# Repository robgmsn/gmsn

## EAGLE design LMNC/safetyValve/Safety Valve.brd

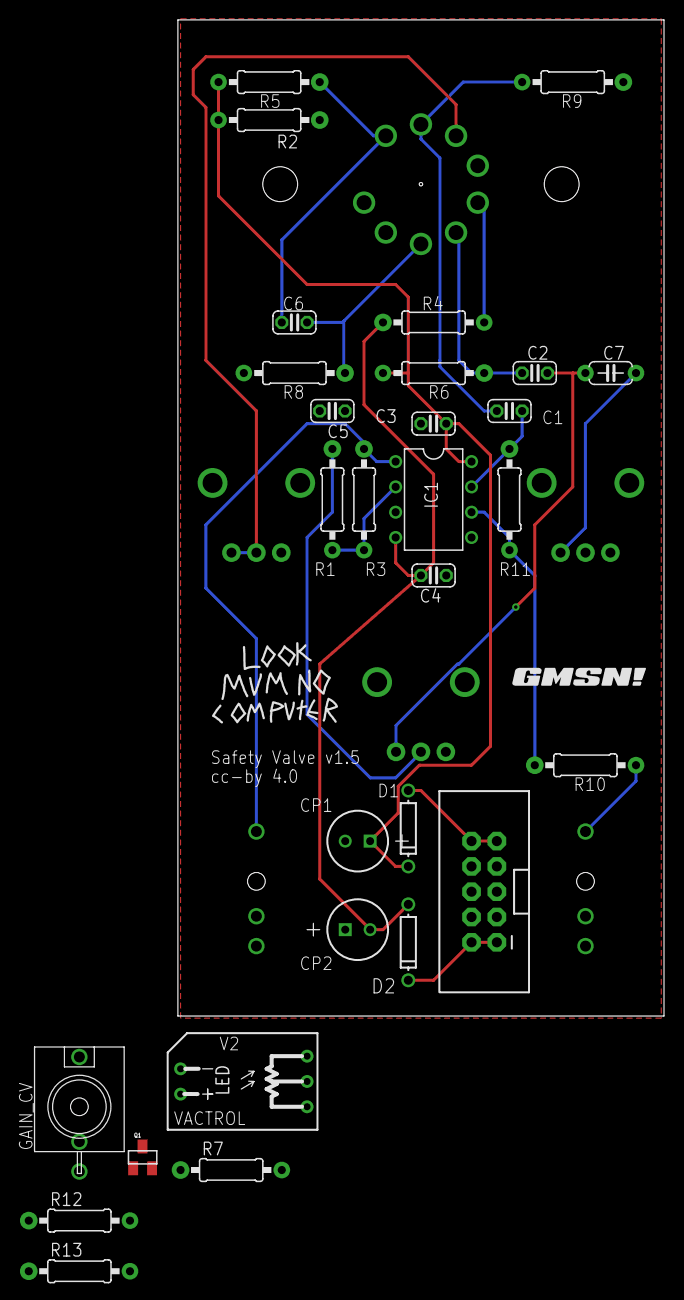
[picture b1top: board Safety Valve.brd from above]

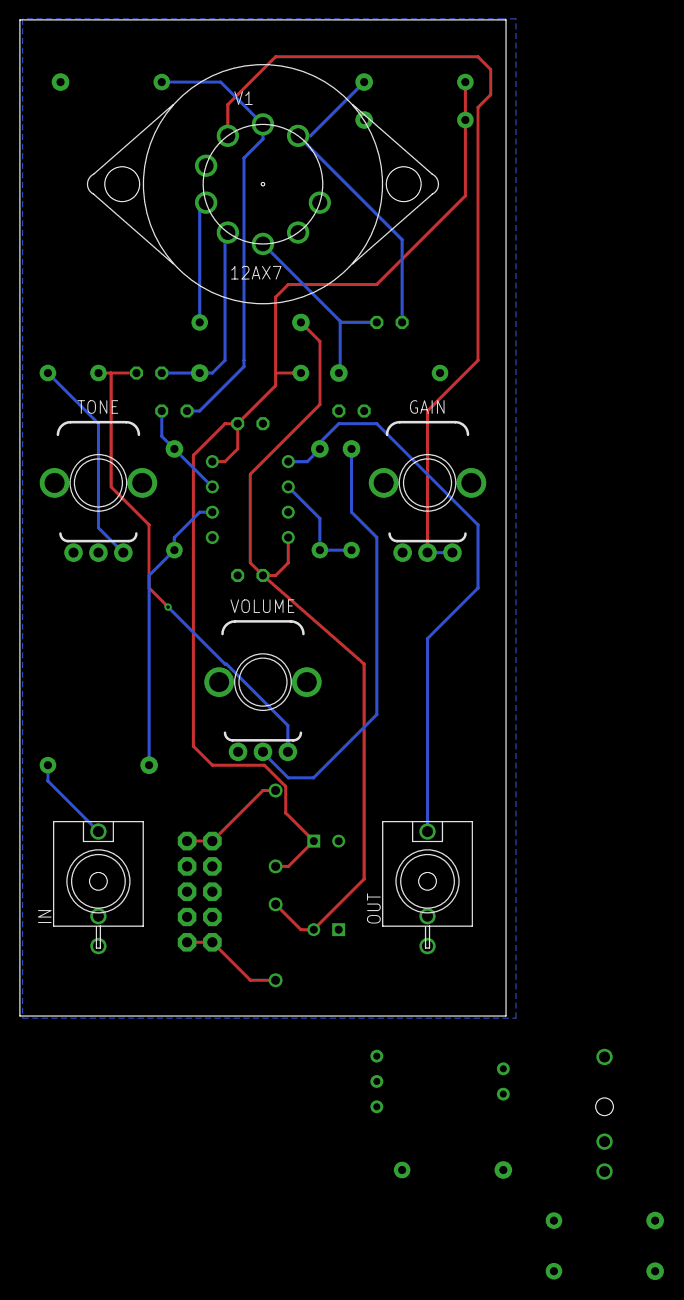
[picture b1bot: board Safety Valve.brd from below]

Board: 2 copper layers, 48.8 x 100.0 mm, 37 parts (6 on the bottom side), 23 nets.

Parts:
C1, C2, C6: 47nF; C025-024X044
C3, C4: 100nF; C025-024X044
C5: 100pF; C025-024X044
C7: 1uF; C050-024X044
CP1, CP2: 10u; SANYO-OSCON_D
D1, D2: 1N4001; DO-41
GAIN: 10k; POTENTIOMETER_9MM
GAIN_CV: SOCKET_MONO_3.5MMPJ301M-12; PJ301M-12
IC1: TL072; DIL08
IN: SOCKET_MONO_3.5MMPJ301M-12; PJ301M-12
JP1: HEADER2X5SHD; 2X5-SHROUDED
OUT: SOCKET_MONO_3.5MMPJ301M-12; PJ301M-12
Q1: SOT23
R1: 470R; 0207/10
R2: 47k; 0207/10
R3: 1M; 0207/10
R4: 27; 0207/10
R5, R6: 12k; 0207/10
R7: 1k; 0207/10
R8, R9: 470k; 0207/10
R10, R11, R12, R13: 100k; 0207/10
TONE: 5k; POTENTIOMETER_9MM
U$1: LMNC_LOGO
U$2: GMSN!_LOGO
V1: 12AX7
V2: VTL5C-2
VOLUME: 100k; POTENTIOMETER_9MM

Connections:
+12V: C3.1, CP1.+, D1.C, IC1.8, R2.2, R5.2, R6.2
-12V: C4.2, CP2.-, D2.A, IC1.4, R4.1
GND: C3.2, C4.1, CP1.-, CP2.+, GAIN.P$1, GAIN_CV.GND, IC1.3, IC1.5, IN.GND, JP1.3, JP1.4, JP1.5, JP1.6, JP1.7, JP1.8, OUT.GND, Q1.2, R8.2, R9.1, R12.1, TONE.P$1, TONE.P$2, V1.P$4, V1.P$8, V2.1, V2.4, VOLUME.P$1
unnamed: GAIN.P$2, GAIN.P$3, V1.P$3, V2.3
unnamed: C5.1, IC1.2, R1.2, R3.2
unnamed: C2.2, C7.1, VOLUME.P$3
unnamed: C5.2, IC1.1, OUT.TIP, R3.1
unnamed: C2.1, R6.1, V1.P$6
unnamed: C6.1, R5.1, V1.P$1
unnamed: C1.2, R2.1, R9.2, V1.P$2
unnamed: C1.1, IC1.7, R11.1
unnamed: R4.2, V1.P$5
unnamed: C6.2, R8.1, V1.P$7
unnamed: D1.A, JP1.9, JP1.10
unnamed: IN.TIP, R10.2
unnamed: D2.C, JP1.1, JP1.2
unnamed: C7.2, TONE.P$3
unnamed: IC1.6, R10.1, R11.2
unnamed: R1.1, VOLUME.P$2
unnamed: GAIN_CV.TIP, R13.1
unnamed: Q1.1, R12.2, R13.2
unnamed: R7.2, V2.2
unnamed: Q1.3, R7.1

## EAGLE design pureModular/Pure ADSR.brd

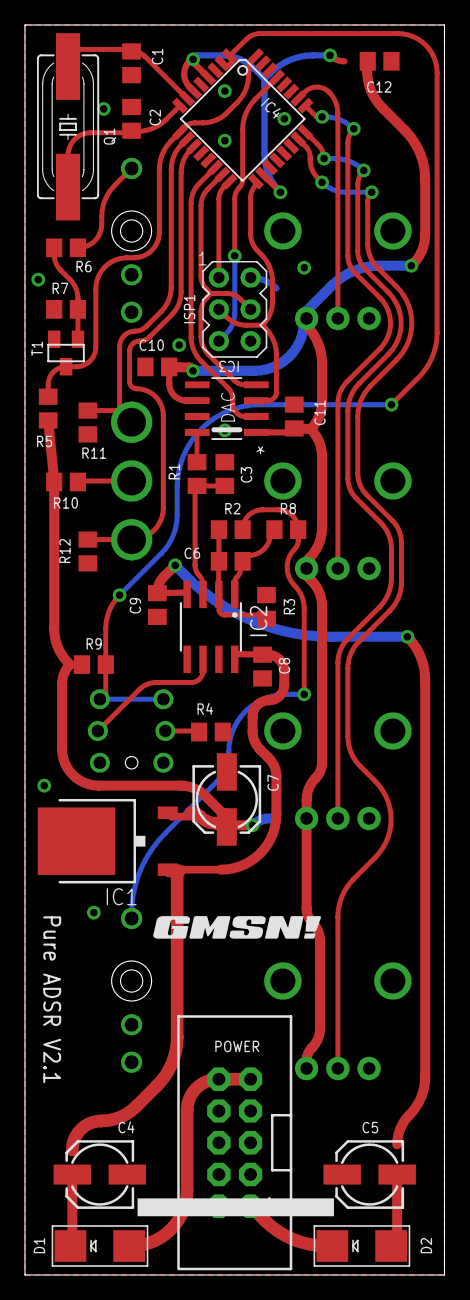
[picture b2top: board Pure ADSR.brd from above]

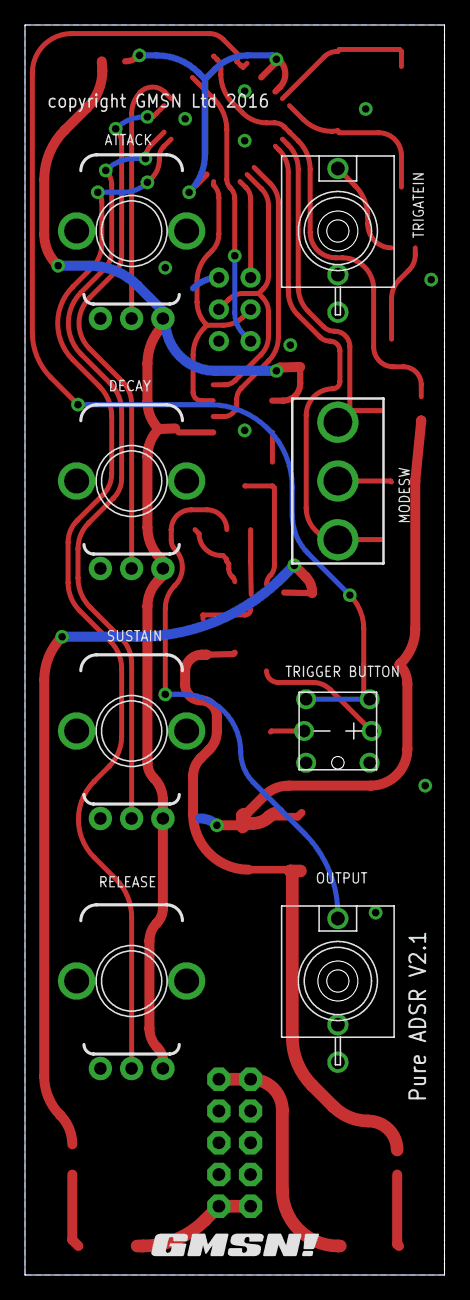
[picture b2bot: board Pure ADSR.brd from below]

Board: 2 copper layers, 33.6 x 100.0 mm, 44 parts (9 on the bottom side), 32 nets.

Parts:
ATTACK: 100k; POTENTIOMETER_9MM
C1, C2: 22p; C0805
C3: 10nF; C0805
C4, C5, C7: 10u; 153CLV-0505
C6: 47p; C0805
C8, C9, C10, C11, C12: 100nF; C0805
D1, D2: STTH102A; SMADIODE
DECAY: 100k; POTENTIOMETER_9MM
IC1: 78M05; TO252
IC2: OPAMP_DUALD; SO08
IC3: MCP4921; SOIC8
IC4: ATMEGA328P; TQFP32-08
ISP1: HEADER2X3-6; AVRISP
MODESW: ON_OFF_ON; TOGGLE_ON_OFF_ON
OUTPUT: SOCKET_MONO_3.5MMPJ301M-12; PJ301M-12
POWER: HEADER2X5SHD; 2X5-SHROUDED
Q1: 20MHz; HC49UP
R1, R3: 56k; R0805
R2: 30k; R0805
R4: 330R; R0805
R5, R9: 10k; R0805
R6, R11, R12: 100k; R0805
R7: 1M; R0805
R8, R10: 1k; R0805
RELEASE: 100k; POTENTIOMETER_9MM
SUSTAIN: 100k; POTENTIOMETER_9MM
T1: MMBT2222A; SOT23
TRIGATEIN: SOCKET_MONO_3.5MMPJ301M-12; PJ301M-12
TRIGGER: PB6149L-5; PB6149L
U$1, U$2: GMSN!_LOGO

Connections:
5V: ATTACK.P$3, C10.1, C11.1, C12.1, DECAY.P$3, IC3.1, IC3.6, IC4.4, IC4.6, IC4.18, ISP1.2, R5.2, R9.2, R10.2, RELEASE.P$3, SUSTAIN.P$3
+5V: C7.+, IC1.2
+12V: C4.+, C8.1, D1.C, IC1.1, IC2.8
-12V: C5.-, C9.2, D2.A, IC2.4
B_TRIG: IC4.1, IC4.2, R9.1, TRIGGER.1, TRIGGER.2
CS: IC3.2, IC4.14
GND: ATTACK.P$1, C1.2, C2.2, C3.2, C4.-, C5.+, C7.-, C8.2, C9.1, C10.2, C11.2, C12.2, DECAY.P$1, IC1.3, IC3.5, IC3.7, IC4.3, IC4.5, IC4.21, ISP1.6, OUTPUT.GND, POWER.3, POWER.4, POWER.5, POWER.6, POWER.7, POWER.8, R3.1, R4.2, R7.1, R11.1, R12.1, RELEASE.P$1, SUSTAIN.P$1, T1.2, TRIGATEIN.GND, TRIGGER.3, TRIGGER.4
MISO: IC4.16, ISP1.1
MOSI: IC3.4, IC4.15, ISP1.4
unnamed: C1.1, IC4.7, Q1.2
unnamed: C2.1, IC4.8, Q1.1
unnamed: IC3.8, R1.1
unnamed: C3.1, IC2.3, IC2.5, R1.2
unnamed: C6.1, IC2.2, R2.1, R3.2
unnamed: OUTPUT.TIP, R2.2, R8.2
unnamed: IC2.6, IC2.7, TRIGGER.A
unnamed: R4.1, TRIGGER.K
unnamed: D1.A, POWER.9, POWER.10
unnamed: D2.C, POWER.1, POWER.2
unnamed: C6.2, IC2.1, R8.1
unnamed: MODESW.2, R10.1
unnamed: R6.1, R7.2, T1.1
unnamed: R6.2, TRIGATEIN.TIP
POT_A: ATTACK.P$2, IC4.26
POT_D: DECAY.P$2, IC4.25
POT_R: IC4.23, RELEASE.P$2
POT_S: IC4.24, SUSTAIN.P$2
RST: IC4.29, ISP1.5
SCK: IC3.3, IC4.17, ISP1.3
T1: IC4.10, MODESW.3, R11.2
T2: IC4.11, MODESW.1, R12.2
TRIG: IC4.9, IC4.32, R5.1, T1.3

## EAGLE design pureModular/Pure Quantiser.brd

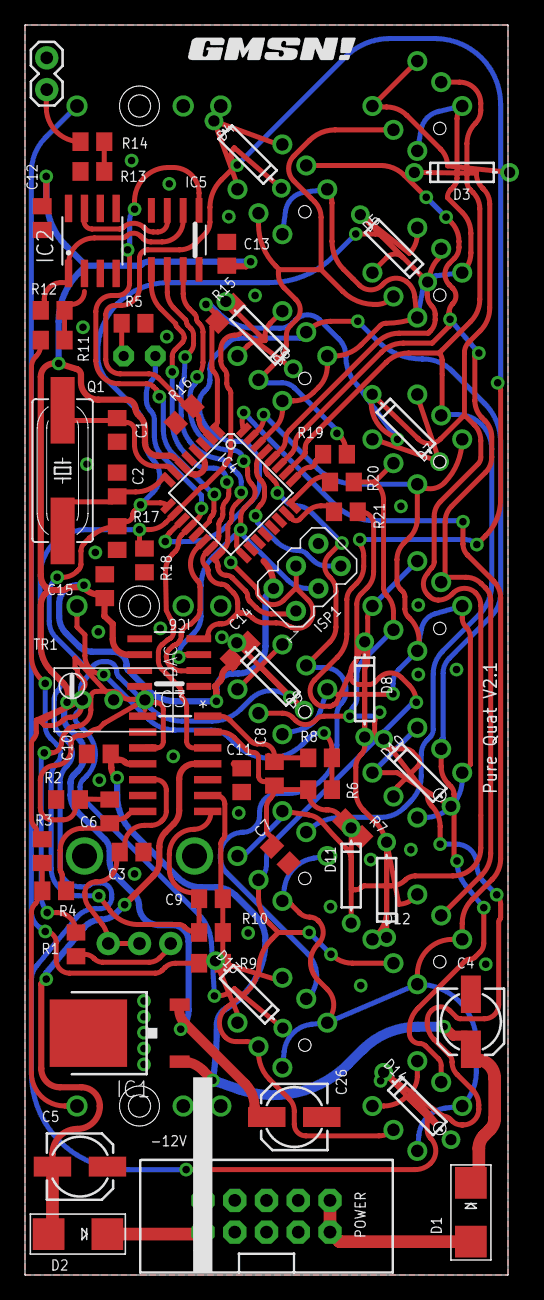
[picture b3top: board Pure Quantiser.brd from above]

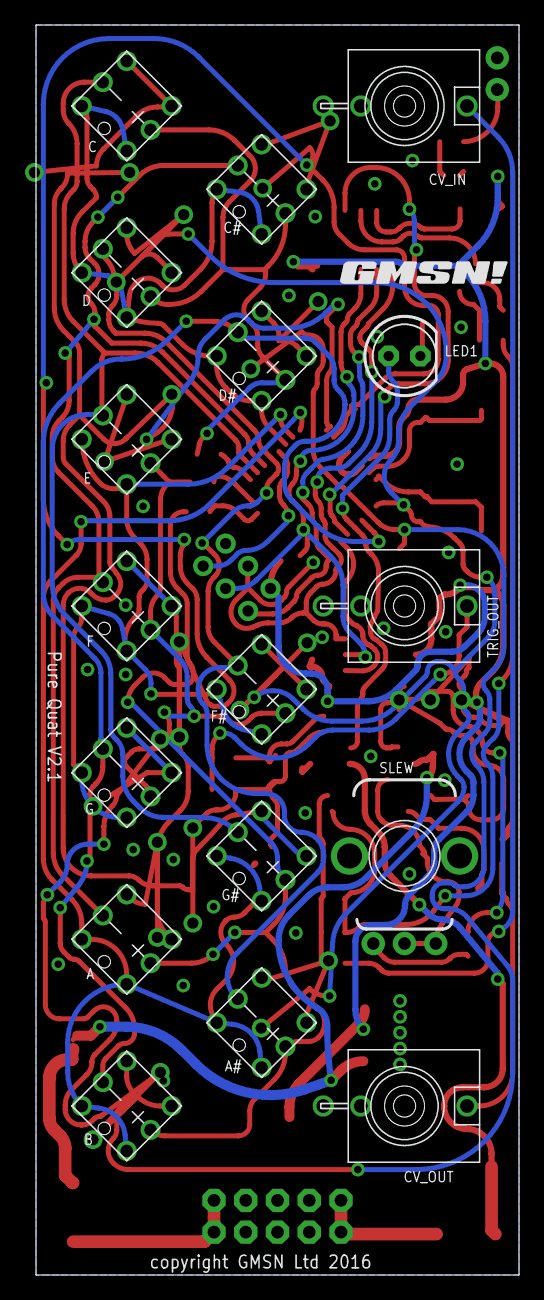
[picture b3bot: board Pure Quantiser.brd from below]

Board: 2 copper layers, 38.6 x 100.0 mm, 81 parts (18 on the bottom side), 64 nets.

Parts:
1, 2, 3, 4, 5, 6, 7, 8, 9, 10, 11, 12: PB6149L-5; PB6149L
C1, C2: 22p; C0805
C3, C7, C8, C10, C11, C12, C13, C14, C15: 100nF; C0805
C4, C5, C26: 10uF; 153CLV-0505
C6: 47p; C0805
C9: 10nF; C0805
CV_IN: PJ301M-12
CV_OUT: PJ301M-12
D1, D2: STTH102A; SMADIODE
D3, D4, D5, D6, D7, D8, D9, D10, D11, D12, D13, D14: 1N914; DO-41
GLIDE: 100k; POTENTIOMETER_9MM
IC1: BA178M05FP; TO252
IC2: TL072; SO08
IC3: TL074; SO14
IC4: ATMEGA328P; TQFP32-08
IC5: MCP3202; SOIC--8
IC6: MCP4921; SOIC8
ISP1: HEADER2X3-6; AVRISP
JP1: HEADER2X5SHD; 2X5-SHROUDED
JP2: HEADER1X2PTH; 1X02
LED1: 5mm; LED5MM
Q1: 20MHz; HC49UP
R1: 200R; R0805
R2, R3, R15, R16, R17, R18: 10k; R0805
R4: 0R; R0805
R5: 1k5; R0805
R6, R7: 1M; R0805
R8: 1k; R0805
R9, R10, R11, R14: 100k; R0805
R12, R13: 49k9; R0805
R19, R20, R21: 100R; R0805
TR1: 10k; TRIMMER_TH
TRIG_OUT: PJ301M-12
U$1, U$2: GMSN!_LOGO

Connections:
5V: C12.1, C13.1, C14.1, C15.1, C26.+, IC1.2, IC2.8, IC4.4, IC4.6, IC4.18, IC5.8, IC6.1, IC6.6, ISP1.2
+12V: C4.+, C10.1, D1.C, IC1.1, IC3.4
-12V: C5.-, C11.2, D2.A, IC3.11
BC_0: 1.3, 1.4, 2.3, 2.4, 3.3, 3.4, 4.3, 4.4, IC4.30
BC_1: 5.3, 5.4, 6.3, 6.4, 7.3, 7.4, 8.3, 8.4, IC4.31
BC_2: 9.3, 9.4, 10.3, 10.4, 11.3, 11.4, 12.3, 12.4, IC4.32
BR_0: D3.C, D7.C, D11.C, IC4.1, R15.2
BR_1: D4.C, D8.C, D12.C, IC4.2, R16.2
BR_2: D5.C, D9.C, D13.C, IC4.9, R17.2
BR_3: D6.C, D10.C, D14.C, IC4.10, R18.2
CS1: IC4.14, IC6.2
CS2: IC4.13, IC5.1
GND: C1.2, C2.2, C3.2, C4.-, C5.+, C7.2, C10.2, C11.1, C12.2, C13.2, C14.2, C15.2, C26.-, CV_IN.GND, CV_IN.NORM, CV_OUT.GND, IC1.3, IC2.3, IC2.4, IC2.5, IC3.10, IC4.3, IC4.5, IC4.21, IC5.4, IC6.5, IC6.7, ISP1.6, JP1.3, JP1.4, JP1.5, JP1.6, JP1.7, JP1.8, JP2.1, R2.1, R5.2, R7.1, R15.1, R16.1, R17.1, R18.1, TRIG_OUT.GND
LC_0: IC4.23, R21.2
LC_1: IC4.24, R20.2
LC_2: IC4.25, R19.2
LR_0: 1.K, 5.K, 9.K, IC4.26
LR_1: 2.K, 6.K, 10.K, IC4.27
LR_2: 3.K, 7.K, 11.K, IC4.28
LR_3: 4.K, 8.K, 12.K, IC4.11
MISO: IC4.16, IC5.6, ISP1.1
MOSI: IC4.15, IC5.5, IC6.4, ISP1.4
unnamed: C1.1, IC4.7, Q1.2
unnamed: C2.1, IC4.8, Q1.1
unnamed: IC3.3, IC6.8
unnamed: IC3.1, IC3.2, R1.1
unnamed: GLIDE.P$1, R1.2
unnamed: C3.1, GLIDE.P$2, GLIDE.P$3, IC3.5
unnamed: R3.1, TR1.1, TR1.2
unnamed: CV_OUT.TIP, R3.2, R4.2
unnamed: D1.A, JP1.9, JP1.10
unnamed: D2.C, JP1.1, JP1.2
unnamed: C6.1, IC3.7, R4.1
unnamed: C6.2, IC3.6, R2.2, TR1.3
unnamed: C7.1, C8.1, IC3.13, R6.1, R7.2
unnamed: LED1.K, R5.1
unnamed: R6.2, R8.2, TRIG_OUT.TIP
unnamed: C8.2, IC3.14, R8.1
unnamed: C9.1, IC3.9, R9.1, R10.2
unnamed: CV_IN.TIP, R9.2
unnamed: IC2.1, IC5.2, R12.1
unnamed: IC2.2, R11.1, R12.2
unnamed: C9.2, IC3.8, R10.1, R11.2
unnamed: 1.1, 1.2, D3.A
unnamed: IC2.7, IC5.3, R13.1
unnamed: IC2.6, R13.2, R14.1
unnamed: JP2.2, R14.2
unnamed: 2.1, 2.2, D4.A
unnamed: 3.1, 3.2, D5.A
unnamed: 4.1, 4.2, D6.A
unnamed: 5.1, 5.2, D7.A
unnamed: 6.1, 6.2, D8.A
unnamed: 7.1, 7.2, D9.A
unnamed: 8.1, 8.2, D10.A
unnamed: 9.1, 9.2, D11.A
unnamed: 10.1, 10.2, D12.A
unnamed: 11.1, 11.2, D13.A
unnamed: 12.1, 12.2, D14.A
unnamed: 1.A, 2.A, 3.A, 4.A, R19.1
unnamed: 5.A, 6.A, 7.A, 8.A, R20.1
unnamed: 9.A, 10.A, 11.A, 12.A, R21.1
RST: IC4.29, ISP1.5
SCK: IC4.17, IC5.7, IC6.3, ISP1.3
TRIG: IC3.12, IC4.12, LED1.A

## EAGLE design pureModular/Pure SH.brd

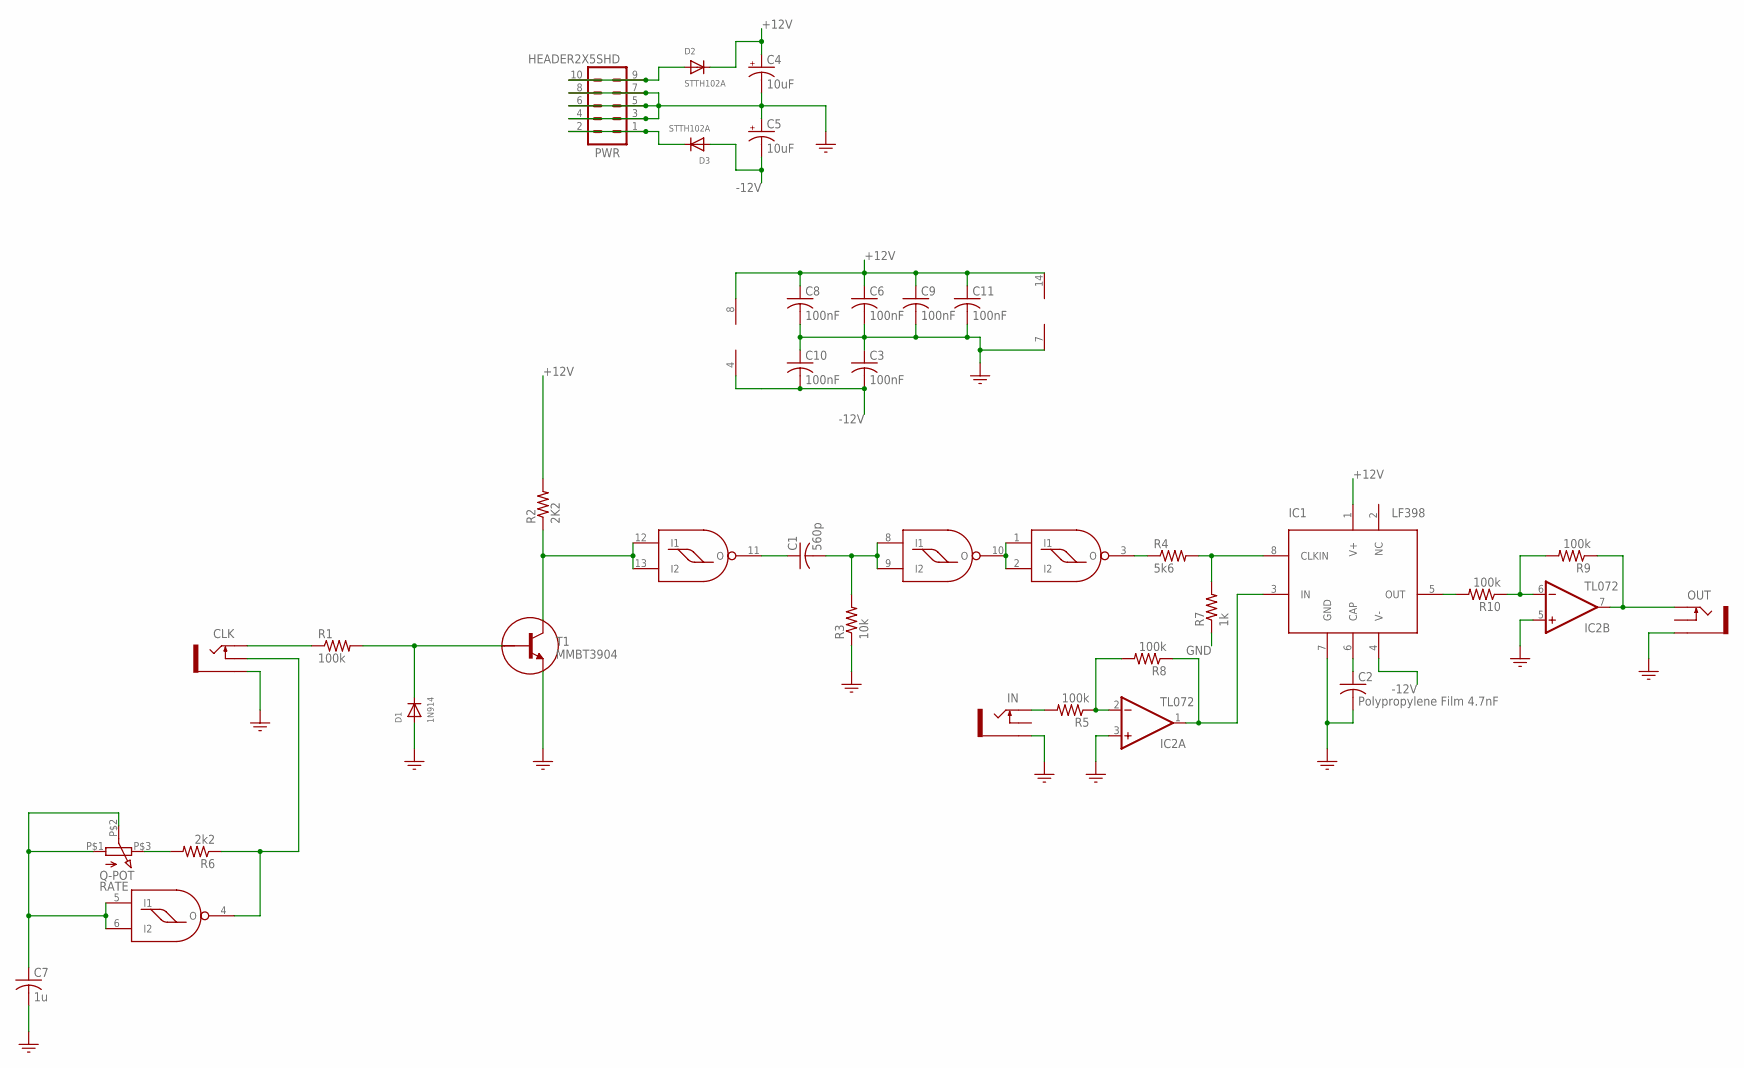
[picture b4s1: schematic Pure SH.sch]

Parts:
C1: 560p; C0805
C2: Polypropylene Film 4.7nF; C050-045X075
C3, C6, C8, C9, C10, C11: 100nF; C0805
C4, C5: 10uF; 153CLV-0505
C7: 1u; C0805
CLK: PJ301M-12
D1: 1N914; DO-41
D2, D3: STTH102A; DO-41
IC1: LF398; SOIC--8
IC2: TL072; SO08
IC3: cd4093; SOIC14
IN: PJ301M-12
OUT: PJ301M-12
PWR: HEADER2X5SHD; 2X5-SHROUDED
R1, R5, R8, R9, R10: 100k; R0805
R2: 2K2; R0805
R3: 10k; R0805
R4: 5k6; R0805
R6: 2k2; R0805
R7: 1k; R0805
RATE: Q-POT; POTENTIOMETER_9MM
T1: MMBT3904; SOT23

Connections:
+12V: C4.+, C6.1, C8.1, C9.1, C11.1, D2.C, IC1.1 (V+), IC2.8 (V+), IC3.14 (V+), R2.2
-12V: C3.2, C5.-, C10.2, D3.A, IC1.4 (V-), IC2.4 (V-)
GND: C2.2, C3.1, C4.-, C5.+, C6.2, C7.2, C8.2, C9.2, C10.1, C11.2, CLK.GND (SLEEVE), D1.A, IC1.7 (GND), IC2.3 (+IN), IC2.5 (+IN), IC3.7 (V-), IN.GND (SLEEVE), OUT.GND (SLEEVE), PWR.3, PWR.4, PWR.5, PWR.6, PWR.7, PWR.8, R3.1, R7.1, T1.2 (E)
unnamed: CLK.TIP, R1.1
unnamed: D1.C, R1.2, T1.1 (B)
unnamed: C1.1, IC3.11 (O)
unnamed: IC3.12 (I1), IC3.13 (I2), R2.1, T1.3 (C)
unnamed: IC3.1 (I1), IC3.2 (I2), IC3.10 (O)
unnamed: IC1.8 (CLKIN), R4.2, R7.2
unnamed: C1.2, IC3.8 (I1), IC3.9 (I2), R3.2
unnamed: IC3.3 (O), R4.1
unnamed: C2.1, IC1.6 (CAP)
unnamed: IN.TIP, R5.2
unnamed: IC2.2 (-IN), R5.1, R8.2
unnamed: R6.2, RATE.P$3 (3)
unnamed: C7.1, IC3.5 (I1), IC3.6 (I2), RATE.P$1 (1), RATE.P$2 (2)
unnamed: CLK.NORM (SWITCH), IC3.4 (O), R6.1
unnamed: IC1.3 (IN), IC2.1 (OUT), R8.1
unnamed: IC1.5 (OUT), R10.2
unnamed: IC2.6 (-IN), R9.2, R10.1
unnamed: IC2.7 (OUT), OUT.TIP, R9.1
unnamed: D2.A, PWR.9, PWR.10
unnamed: D3.C, PWR.1, PWR.2

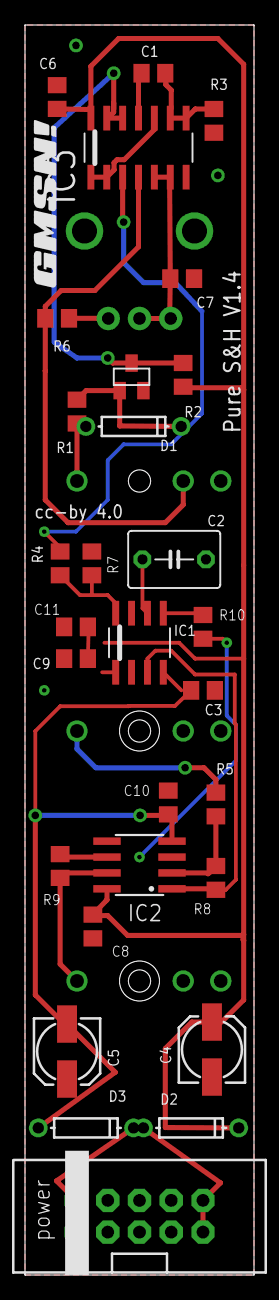
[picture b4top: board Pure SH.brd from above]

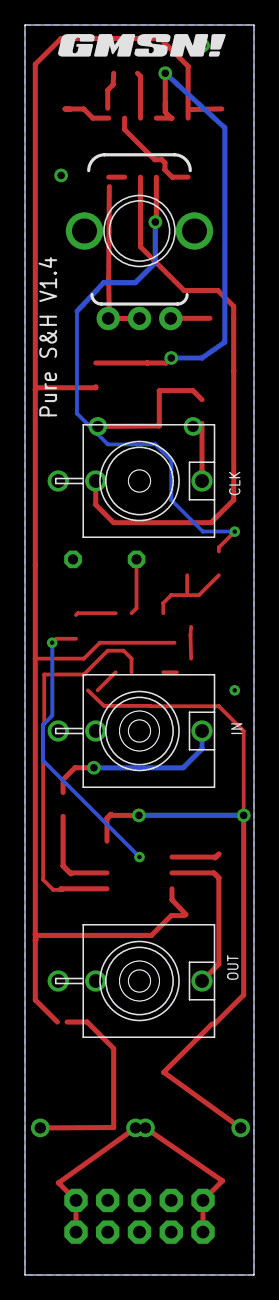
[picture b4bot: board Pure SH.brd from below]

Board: 2 copper layers, 18.3 x 100.0 mm, 35 parts (5 on the bottom side), 23 nets.

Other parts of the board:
U$2, U$3: GMSN!_LOGO

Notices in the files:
LMNC/safetyValve/Safety Valve.brd:
cc-by 4.0
pureModular/Pure ADSR.brd:
copyright GMSN Ltd 2016
